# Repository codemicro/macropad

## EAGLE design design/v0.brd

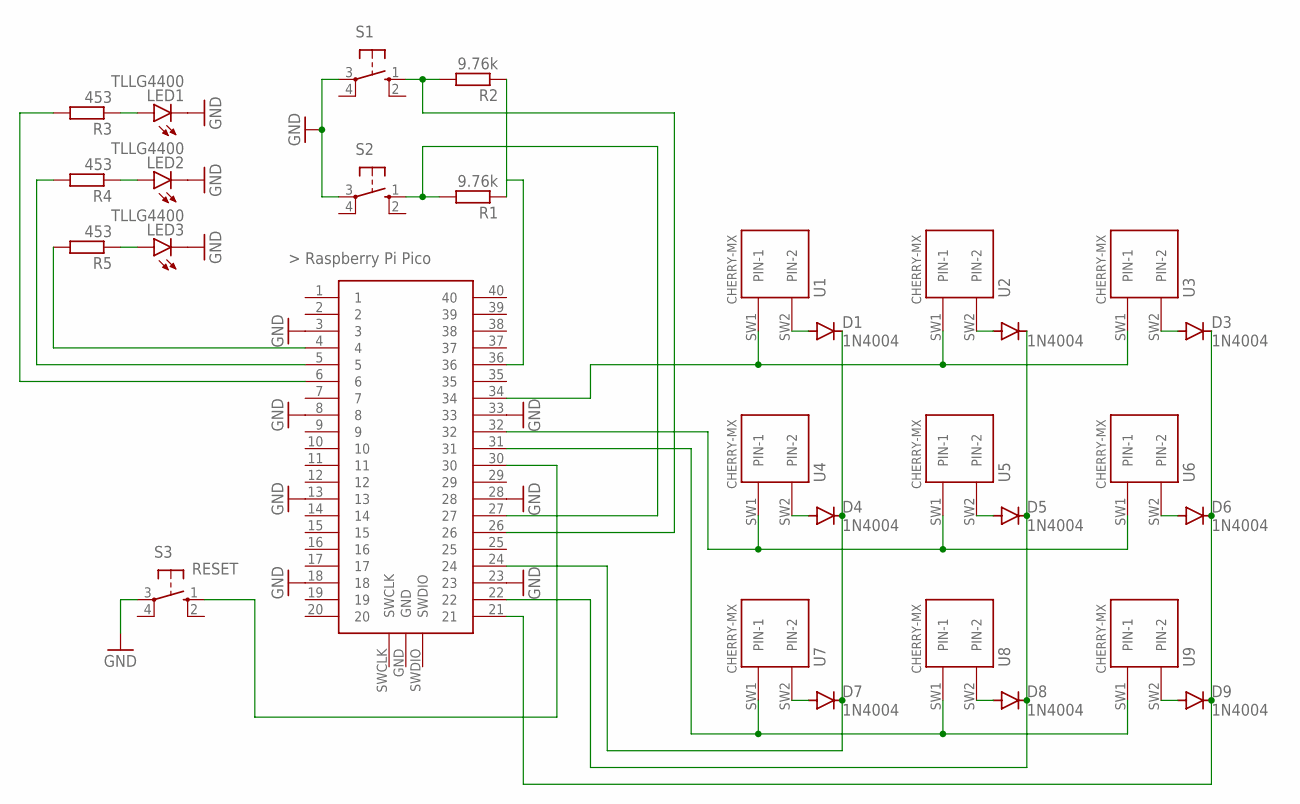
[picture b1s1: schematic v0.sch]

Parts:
D1, D2, D3, D4, D5, D6, D7, D8, D9: 1N4004; DO41-10
LED1, LED2, LED3: TLLG4400; LED3MM
R1, R2: 9.76k; VMTA55
R3, R4, R5: 453; VMTA55
S1, S2: 10-XX; B3F-10XX
S3: RESET; B3F-10XX
U1, U2, U3, U4, U5, U6, U7, U8, U9: CHERRY-MX
U$1: RASPBERRY-PI-PICO_TH; FT_RASPBERRY-PI-PICO_TH

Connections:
GND: LED1.K (C), LED2.K (C), LED3.K (C), S1.3, S2.3, S3.3, U$1.3, U$1.8, U$1.13, U$1.18, U$1.23, U$1.28, U$1.33, U$1.38
unnamed: LED2.A, R4.1
unnamed: LED1.A, R3.1
unnamed: LED3.A, R5.1
unnamed: R1.2, S2.1 (S), U$1.27
unnamed: R5.2, U$1.4
unnamed: R4.2, U$1.5
unnamed: R3.2, U$1.6
unnamed: R2.2, S1.1 (S), U$1.26
unnamed: R1.1, R2.1, U$1.36
unnamed: S3.1 (S), U$1.30
unnamed: D1.C, D4.C, D7.C, U$1.24
unnamed: D2.C, D5.C, D8.C, U$1.22
unnamed: D3.C, D6.C, D9.C, U$1.21
unnamed: D6.A, U6.SW2 (PIN-2)
unnamed: D3.A, U3.SW2 (PIN-2)
unnamed: D9.A, U9.SW2 (PIN-2)
unnamed: D8.A, U8.SW2 (PIN-2)
unnamed: D5.A, U5.SW2 (PIN-2)
unnamed: D2.A, U2.SW2 (PIN-2)
unnamed: D1.A, U1.SW2 (PIN-2)
unnamed: D4.A, U4.SW2 (PIN-2)
unnamed: D7.A, U7.SW2 (PIN-2)
unnamed: U1.SW1 (PIN-1), U2.SW1 (PIN-1), U3.SW1 (PIN-1), U$1.34
unnamed: U4.SW1 (PIN-1), U5.SW1 (PIN-1), U6.SW1 (PIN-1), U$1.32
unnamed: U7.SW1 (PIN-1), U8.SW1 (PIN-1), U9.SW1 (PIN-1), U$1.31

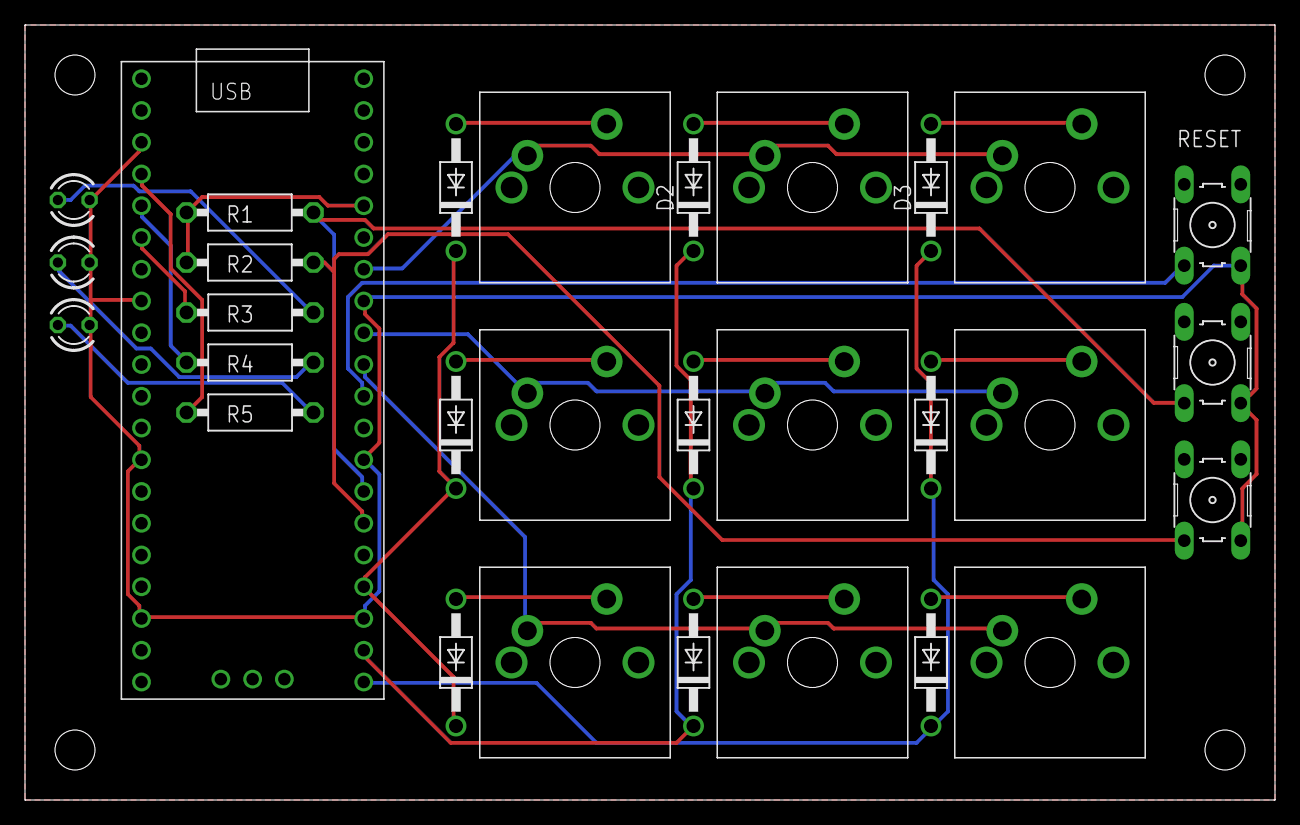
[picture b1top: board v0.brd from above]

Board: 2 copper layers, 100.0 x 62.0 mm, 30 parts (0 on the bottom side), 26 nets.

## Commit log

2021-01-30 Setup commit
2021-01-30 Fix README.md
2021-01-31 Switch to CircuitPython, add bundler.json for dependencies
2021-01-31 Switch to using GP13 tied high
2021-01-31 Add current schematic
2021-02-01 Add Eagle schematic
2021-02-02 Add Cherry MX Eagle CAD library to README.md
2021-02-02 Update schematic
2021-02-02 Fix Cherry MX Eagle lib typo
2021-02-05 Update for matrix
2021-02-05 Fix resistor locations on buttons
2021-02-05 Add new image and move image path
2021-02-05 Update LED resistor values
2021-02-05 Add initial prototype page
2021-02-05 Switch keyswitches
2021-02-06 Switched component pins, added ground plane
2021-02-06 Added board design
2021-02-06 Update image
2021-02-07 Update net class width, swap R1/R2 names
2021-02-07 Add silkscreen text, move labels, perform routing
2021-02-07 Update .gitignore for Eagle CAD files
2021-02-11 Add missing ground marker
2021-02-11 Silkscreen tweaks
2021-02-11 Update gitignore
2021-02-11 Add initials bitmap script
2021-02-11 Remove useless silkscreen labels
2021-02-11 Move trace that was kinda close to a pad
2021-02-15 Add pinout and mapping files for Python firmware
2021-02-16 Add keyboard controller class
2021-02-20 Add rev0 board test
2021-02-20 Add initial rev0 firmware
2021-02-21 Add firmware layer support
2021-02-21 Add consumer control key support
2021-02-21 Rename v0.* -> rev0.*
2021-02-21 Update images
2021-02-21 Add scans of rev0 boards
2021-02-21 Rename some images for rev0
2021-02-22 Restructure firmware directory
2021-02-22 Black code formatting
2021-02-22 Add type checks and assertions to main.py for user_mappings
2021-02-22 Remove prototype docs
2021-02-22 Add licencing
2021-02-22 Remove double licence header
2021-02-25 Add rev0 specification
2021-02-25 Add initial rev1 notes
